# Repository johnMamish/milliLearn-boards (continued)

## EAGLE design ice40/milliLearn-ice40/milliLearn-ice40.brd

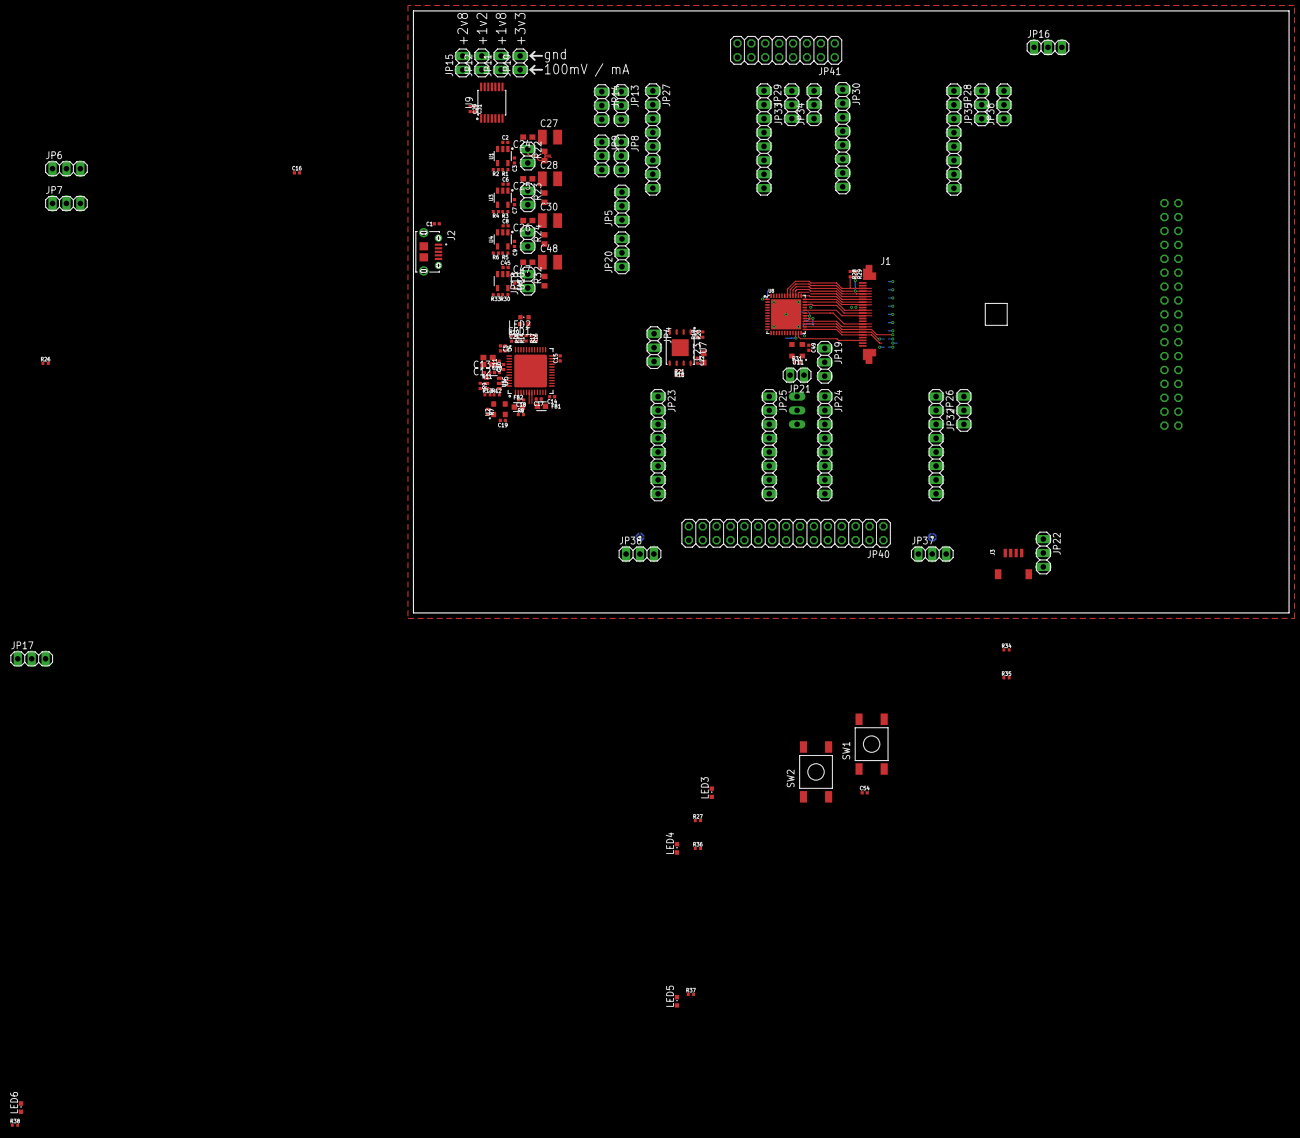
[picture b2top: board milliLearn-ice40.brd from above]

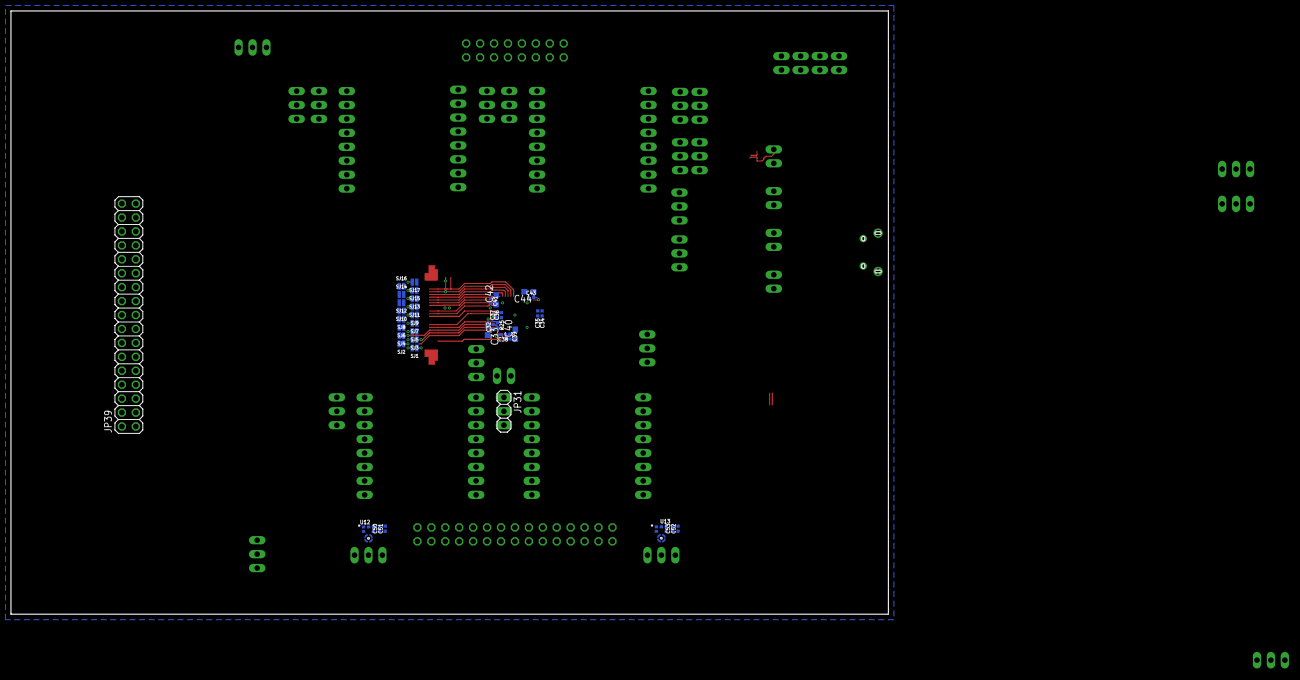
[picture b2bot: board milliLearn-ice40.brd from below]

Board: 4 copper layers, 160.0 x 110.0 mm, 176 parts (39 on the bottom side), 124 nets.

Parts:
C1: C0402_COMPACT
C2, C3, C6, C7, C8, C9, C29, C34, C36, C45, C46: 1u; C0402_COMPACT
C4, C5, C10, C11, C14, C15, C16, C17, C18, C19, C20, C22, C31, C32, C35, C37, C38, C39, C41, C43, C49, C50, C52, C54: 100n; C0402_COMPACT
C12, C13, C23, C24, C25, C26, C33, C40, C42, C44, C47: 4.7u; C0603
C21: 10n; C0402_COMPACT
C27, C28, C30, C48: 22u; C1210
C51, C53: 220p; C0402_COMPACT
FB1, FB2: BLM18KG601SN1D
J1: SFV24R-2STE1HLF
J2: 10118194-0001LF; AMPHENOL_10118194-0001LF
J3: SM04B-SRSS-TB(LF)(SN)
JP1, JP2, JP3, JP10, JP11, JP12, JP15, JP18, JP21: 1X02
JP4, JP5, JP6, JP7, JP8, JP9, JP13, JP14, JP16, JP17, JP19, JP20, JP22, JP31, JP32, JP33, JP34, JP35, JP36, JP37, JP38: 1X03
JP23, JP24, JP25, JP26, JP27, JP28, JP29, JP30: 1X08
JP39: 2X17
JP40: 2X15
JP41: 2X08
LED1, LED2, LED3, LED4, LED5, LED6: CHIPLED_0603
R1: 75k 1%; R0402_COMPACT
R2, R6: 24k 1%; R0402_COMPACT
R3: 20k 1%; R0402_COMPACT
R4: 16k 1%; R0402_COMPACT
R5, R8, R33: 12k 1%; R0402_COMPACT
R7, R10, R11, R18, R19, R20, R21, R26, R28, R29, R31: 10k; R0402_COMPACT
R9: 2.2k; R0402_COMPACT
R12, R13: DNP; R0402_COMPACT
R14, R15, R27, R36, R37, R38: 1k; R0402_COMPACT
R16, R34, R35: 4.7k; R0402_COMPACT
R17: 12k; R0402_COMPACT
R22, R23, R24, R32: 0.5 1%; R0603
R25: 100; R0402_COMPACT
R30: 30k 1%; R0402_COMPACT
SJ1, SJ2, SJ3, SJ4, SJ5, SJ6, SJ7, SJ8, SJ9, SJ10, SJ11, SJ12, SJ13, SJ14, SJ15, SJ16, SJ17: JUMPER-SMT_2_NC_PASTE_NO-SILK; SMT-JUMPER_2_NC_PASTE_NO-SILK
SW1, SW2: TE_FSMJSMA
U1, U3, U4, U10: AP7366-W5-7
U2, U11: DSC6111CI2A-012.0000
U5: MICROBUILDER_FT232HQ; MICROBUILDER_QFN48_8MM
U6: MICROCHIP_93LC76B; MICROCHIP_SOT23-6
U7: MT25QL128ABA1EW7
U8: ICE40UP5K/3K-SG48
U9: INA4180A4IPWR
U12, U13: SPH0645LM4H-B

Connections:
+1V2: C9.2, JP3.1, JP5.1, JP20.1, R5.1, U4.5
+1V2_METERED: C26.1, C30.1, JP5.3, JP20.3, R24.2, U9.9
+1V8: C7.2, JP2.1, JP9.1, JP14.1, JP16.1, JP34.1, JP36.1, R3.1, U3.5
+1V8_METERED: C25.1, C28.1, JP9.3, JP14.3, JP16.3, JP34.3, JP36.3, R23.2, U9.6
+2V8: C46.2, JP17.1, JP18.1, R30.1, U10.5
+2V8_METERED: C47.1, C48.1, JP17.3, R32.2, U9.13
+3V3: C3.2, C29.2, C31.2, JP1.1, JP4.1, JP6.1, JP7.1, JP8.1, JP13.1, JP19.1, JP22.1, JP31.1, JP32.1, JP33.1, JP35.1, JP37.1, JP38.1, R1.1, R27.1, R36.1, R37.1, R38.1, U1.5, U9.4
+3V3_METERED: C24.1, C27.1, JP4.3, JP6.3, JP7.3, JP8.3, JP13.3, JP19.3, JP22.3, JP31.3, JP32.3, JP33.3, JP35.3, JP37.3, JP38.3, R22.2, U9.2
CONFIG_FLASH_+3V3: C22.2, C23.1, JP4.2, R18.1, R19.1, R20.1, R21.1, U7.8
D+: J2.3, U5.7
D-: J2.2, U5.6
FT232_OSC_12M: U2.P$3, U5.1
FT232_VCCD: C11.2, C13.1, C14.2, C15.2, C16.2, C19.2, C20.2, FB1.1, FB2.1, LED1.A, LED2.A, R7.1, R10.1, R11.1, R12.1, R13.1, U2.P$4, U5.12, U5.24, U5.39, U5.46, U6.6
GND: C1.1, C2.1, C3.1, C4.1, C5.1, C6.1, C7.1, C8.1, C9.1, C10.1, C11.1, C12.2, C13.2, C14.1, C15.1, C16.1, C17.1, C18.1, C19.1, C20.1, C21.1, C22.1, C23.2, C24.2, C25.2, C26.2, C27.2, C28.2, C29.1, C30.2, C31.1, C32.1, C33.2, C34.1, C35.1, C36.1, C37.1, C38.1, C39.1, C40.2, C41.1, C42.2, C43.1, C44.2, C45.1, C46.1, C47.2, C48.2, C49.1, C50.1, C51.1, C52.1, C53.1, C54.1, J1.P$2, J1.P$15, J2.5, J2.S1, J2.S2, J2.S3, J2.S4, J2.S5, J2.S6, J3.P$1, JP10.2, JP11.2, JP12.2, JP15.2, JP21.2, JP23.2, JP23.4, JP23.6, JP23.7, JP23.8, JP24.2, JP24.4, JP24.6, JP24.7, JP24.8, JP25.2, JP25.4, JP25.6, JP25.8, JP26.2, JP26.4, JP26.6, JP26.8, JP27.2, JP27.4, JP27.6, JP27.7, JP27.8, JP28.2, JP28.4, JP28.6, JP28.7, JP28.8, JP29.2, JP29.4, JP29.6, JP29.8, JP30.2, JP30.4, JP30.6, JP30.8, JP39.2, JP39.4, JP39.6, JP39.8, JP39.10, JP39.12, JP39.14, JP39.16, JP39.18, JP39.20, JP39.22, JP39.24, JP39.26, JP39.28, JP39.30, JP39.32, JP39.34, JP40.2, JP40.4, JP40.6, JP40.8, JP40.10, JP40.12, JP40.14, JP40.16, JP40.18, JP40.20, JP40.22, JP40.24, JP40.26, JP40.28, JP40.30, JP41.2, JP41.4, JP41.6, JP41.8, JP41.10, JP41.12, JP41.14, JP41.16, LED6.C, R2.2, R4.2, R6.2, R8.1, R17.2, R33.2, SW1.P$3, SW1.P$4, SW2.P$3, SW2.P$4, U1.2, U2.P$2, U3.2, U4.2, U5.4, U5.9, U5.10, U5.11, U5.22, U5.23, U5.35, U5.36, U5.41, U5.42, U5.47, U5.48, U5.THERMAL, U6.2, U7.4, U7.9, U8.49, U9.11, U10.2, U11.P$2, U12.P$2, U12.P$3@0, U12.P$3@1, U12.P$3@2, U12.P$3@3, U13.P$3@0, U13.P$3@1, U13.P$3@2, U13.P$3@3
HM01B0_+1V8: J1.P$10, JP16.2, R28.1, R29.1
HM01B0_+2V8: J1.P$4, J1.P$11, JP17.2
HM01B0_D0: J1.P$14, SJ9.1, U8.35
HM01B0_D1: J1.P$3, SJ1.1, U8.23
HM01B0_D2: J1.P$9, SJ6.1, U8.31
HM01B0_D3: J1.P$5, SJ2.1, U8.25
HM01B0_D4: J1.P$12, SJ7.1, U8.32
HM01B0_D5: J1.P$20, SJ14.1, U8.40
HM01B0_D6: J1.P$19, SJ13.1, U8.39
HM01B0_D7: J1.P$13, SJ8.1, U8.34
HM01B0_HS: J1.P$16, SJ10.1, U8.36
HM01B0_INT: J1.P$18, LED3.C, SJ12.1, U8.38
HM01B0_MCK: J1.P$8, SJ5.1, U8.28
HM01B0_PCLK: J1.P$17, SJ11.1, U8.37
HM01B0_SCL: J1.P$21, R29.2, SJ15.1, U8.41
HM01B0_SDA: J1.P$22, R28.2, SJ16.1, U8.42
HM01B0_TRIG: J1.P$7, LED5.C, SJ4.1, U8.27
HM01B0_VS: J1.P$6, SJ3.1, U8.26
I2S_WS: JP40.29, U8.21, U12.P$1, U13.P$1
ICE40_+1V2_CORE: C34.2, C35.2, C36.2, C37.2, JP20.2, U8.5, U8.30
ICE40_+1V2_PLL: JP5.2, R25.1
ICE40_CRESETB: C54.2, R26.2, SW1.P$1, SW1.P$2, U5.20, U8.8
ICE40_FLASH_CIPO: JP40.21, JP40.27, U5.15, U7.2, U8.17, U12.P$6, U13.P$6
ICE40_FLASH_COPI: JP40.15, LED4.C, U5.14, U7.5, U8.14
ICE40_FLASH_PS: JP40.19, R19.2, U5.17, U7.1, U8.16
ICE40_FLASH_SCK: JP40.17, R18.2, U5.13, U7.6, U8.15, U12.P$4, U13.P$4
ICE40_GPIO43: LED6.A, R38.2, SJ17.1, SW2.P$1, SW2.P$2, U8.43
ICE40_OSC_12M: JP41.1, U8.20, U11.P$3
ICE40_OSC_VCC: C49.2, JP19.2, R31.1, U11.P$4
ICE40_SPI_VCCIO1: C39.2, C40.1, JP7.2, R26.1, U8.22
ICE40_VCCIO0: C41.2, C42.1, JP8.2, JP9.2, U8.33
ICE40_VCCIO2: C43.2, C44.1, JP13.2, JP14.2, U8.1
ICE40_VCCPLL: C32.2, C33.1, R25.2, U8.29
ICE40_VPP2V5_+3V3: C38.2, JP6.2, U8.24
MEM1_!HOLD: JP25.3, JP26.3, JP40.13, U8.13
MEM1_!WP: JP23.5, JP24.5, JP40.11, U8.12
MEM1_CIPO: JP23.3, JP24.3, JP40.9, U8.11
MEM1_COPI: JP25.7, JP26.7, JP40.25, U8.19
MEM1_PS1: JP23.1, JP40.5, U8.9
MEM1_PS2: JP24.1, JP40.7, U8.10
MEM1_SCK: JP25.5, JP26.5, JP40.23, U8.18
MEM1_VCC1: JP25.1, JP31.2
MEM1_VCC2: JP26.1, JP32.2
MEM2_!WP: JP27.5, JP28.5, JP41.9, U8.48
MEM2_CIPO1: JP27.3, JP41.7, U8.47
MEM2_CIPO2: JP28.3, U8.4
MEM2_COPI1: JP29.7, JP41.11, U8.2
MEM2_COPI2: JP30.7, U8.44
MEM2_PS1: JP27.1, JP41.3, U8.45
MEM2_PS2: JP28.1, JP41.5, U8.46
MEM2_SCK: JP29.5, JP30.5, JP41.13, U8.3
MEM2_VCC1: JP29.1, JP33.2, JP34.2
MEM2_VCC2: JP30.1, JP35.2, JP36.2
MIC1_VCC: C50.2, C51.2, JP37.2, U12.P$5
MIC2_VCC: C52.2, C53.2, JP38.2, U13.P$2, U13.P$5
unnamed: R5.2, R6.1, U4.4
unnamed: R1.2, R2.1, U1.4
unnamed: JP1.2, R22.1, U9.3
unnamed: C18.2, FB2.2, U5.3
unnamed: C17.2, FB1.2, U5.8
unnamed: R3.2, R4.1, U3.4
unnamed: R7.2, U2.P$1
unnamed: R9.1, R11.2, U6.1
unnamed: R8.2, U5.5
unnamed: R9.2, U5.43, U6.3
unnamed: R13.2, U5.45, U6.5
unnamed: R12.2, U5.44, U6.4
unnamed: R14.1, U5.32
unnamed: C21.2, R10.2, U5.34
unnamed: LED1.C, R14.2
unnamed: R16.2, R17.1, U5.31
unnamed: R15.1, U5.33
unnamed: LED2.C, R15.2
unnamed: R20.2, U7.3
unnamed: R21.2, U7.7
unnamed: JP2.2, R23.1, U9.5
unnamed: JP3.2, R24.1, U9.10
unnamed: JP10.1, U9.1
unnamed: JP11.1, U9.7
unnamed: JP12.1, U9.8
unnamed: JP15.1, U9.14
unnamed: R30.2, R33.1, U10.4
unnamed: JP18.2, R32.1, U9.12
unnamed: JP21.1, R31.2, U11.P$1
unnamed: LED3.A, R27.2
unnamed: LED4.A, R36.2
unnamed: LED5.A, R37.2
unnamed: JP39.1, SJ1.2
unnamed: JP39.3, SJ2.2
unnamed: JP39.5, SJ3.2
unnamed: JP39.7, SJ4.2
unnamed: JP39.9, SJ5.2
unnamed: JP39.11, SJ6.2
unnamed: JP39.13, SJ7.2
unnamed: JP39.15, SJ8.2
unnamed: JP39.17, SJ9.2
unnamed: JP39.19, SJ10.2
unnamed: JP39.21, SJ11.2
unnamed: JP39.23, SJ12.2
unnamed: JP39.25, SJ13.2
unnamed: JP39.27, SJ14.2
unnamed: JP39.29, SJ15.2
unnamed: JP39.31, SJ16.2
unnamed: JP39.33, SJ17.2
QWIIC_+3V3: J3.P$2, JP22.2, R34.1, R35.1
QWIIC_SCL: J3.P$4, JP40.3, R35.2, U8.7
QWIIC_SDA: J3.P$3, JP40.1, R34.2, U8.6
VCCA: C4.2, U5.37
VCCCORE: C5.2, U5.38
VUSB: C1.2, C2.2, C6.2, C8.2, C10.2, C12.1, C45.2, J2.1, R16.1, U1.1, U1.3, U3.1, U3.3, U4.1, U4.3, U5.40, U10.1, U10.3

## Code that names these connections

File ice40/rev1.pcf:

# nextpnr pin constraint file for all pins in this design

# gpio bank 0
set_io -nowarn hm01b0_pixdata[1]   23
set_io -nowarn hm01b0_pixdata[3]   25
set_io -nowarn hm01b0_vsync        26
set_io -nowarn hm01b0_trig         27
set_io -nowarn hm01b0_mck          28
set_io -nowarn hm01b0_pixdata[2]   31
set_io -nowarn hm01b0_pixdata[4]   32
set_io -nowarn hm01b0_pixdata[7]   34
set_io -nowarn hm01b0_pixdata[0]   35
set_io -nowarn hm01b0_hsync        36
set_io -nowarn hm01b0_pixclk       37
set_io -nowarn hm01b0_int          38
set_io -nowarn hm01b0_pixdata[6]   39
set_io -nowarn hm01b0_pixdata[5]   40
set_io -nowarn hm01b0_scl          41
set_io -nowarn hm01b0_sda          42
set_io -nowarn gpio43_hiz          43

# gpio bank 2
set_io -nowarn mem2_ps1      44
set_io -nowarn mem2_cipo1    45
set_io -nowarn mem2_copi1    46
set_io -nowarn mem2_ps2      47
set_io -nowarn mem2_cipo2    48
set_io -nowarn mem2_nwp      2
set_io -nowarn mem2_sck      3
set_io -nowarn mem2_copi2    4

# gpio bank 1
set_io -nowarn mem1_cipo     6
set_io -nowarn mem1_nwp      7
set_io -nowarn mem1_ps1      9
set_io -nowarn mem1_nhold    10
set_io -nowarn mem1_sck      11
set_io -nowarn mem1_copi     12
set_io -nowarn mem1_ps2      13
set_io -nowarn uart_tx_config_copi       14
set_io -nowarn mic_bck_config_sck        15
set_io -nowarn config_ps                 16
set_io -nowarn mic_ws_config_cipo        17
set_io -nowarn mic_data                  18
set_io -nowarn qwiic_sda                 19
set_io -nowarn osc_12m                   20
set_io -nowarn qwiic_scl                 21

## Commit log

2020-08-03 iCE40 board wip
2020-08-04 pcb-ng board wip
2020-08-05 routing for pcbng variant wip
2020-08-05 first pass of routing done
2020-08-06 fix hm01b0 connector footprint
2020-08-26 add pcf file for rev 1
